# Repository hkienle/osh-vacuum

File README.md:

# Open Source Vacuum Cleaner

> **📝 Note:** This repository is currently being populated with information. Content and documentation are being added progressively.

---

## About

This repository contains the Open Source Vacuum Cleaner project, an open-source hardware and software solution for building custom vacuum cleaners. The project includes complete PCB designs, ESP32-S3 based firmware, and a web-based control interface.

The system is designed to control high RPM impellers for vacuum machines, featuring motor control, real-time monitoring (RPM, temperature, battery voltage), WiFi connectivity, and a modern web interface.

## Project Structure

```
osh-vacuum/
├── Hardware/              # PCB designs and hardware documentation
│   └── PCB_Bench_Prototype/  # Benchtop prototype board design
│       ├── README.md         # Hardware documentation and BOM
│       └── Production/       # Manufacturing files
├── Firmware/              # ESP32-S3 firmware and web interface
│   ├── README.md          # Firmware documentation, pin assignments, build instructions
│   ├── src/               # Firmware source code
│   └── ui/                # React-based web interface
└── README.md              # This file
```

### Hardware

The hardware design includes:
- ESP32-S3 microcontroller with WiFi and BLE
- Motor control with Infineon ProFet for high-side switching
- 5 RGB LEDs (WS2812B) and 3 customizable buttons
- Battery voltage monitoring (15-32V input)
- Temperature monitoring via thermistor
- Tachometer input for RPM measurement
- Break-off sections for flexible form factors

📖 **[Hardware Documentation →](Hardware/PCB_Bench_Prototype/README.md)**

### Firmware

The firmware provides:
- Motor speed control (0-100% PWM)
- Real-time monitoring (RPM, temperature, battery voltage)
- WiFi access point with web server
- WebSocket communication for live updates
- React-based web interface

📖 **[Firmware Documentation →](Firmware/README.md)**

## Quick Start

1. **Hardware**: Review the [PCB documentation](Hardware/PCB_Bench_Prototype/README.md) for board assembly
2. **Firmware**: Follow the [firmware build and upload instructions](Firmware/README.md)
3. **Frontend**: Build and upload the web interface as described in the firmware README

## Status

**Current Phase**: Benchtop Prototype

The current board design is untested and represents the benchtop prototype phase. All designs and firmware are provided as-is for development and testing purposes.

## License

This project is licensed under the **CERN Open Hardware Licence - Strongly Reciprocal (CERN OHL-S v2)**.

The full license text is available at: [cern_ohl_s_v2.txt](https://gitlab.com/ohwr/project/cernohl/-/wikis/uploads/819d71bea3458f71fba6cf4fb0f2de6b/cern_ohl_s_v2.txt)

---

*More information at [HackMD - Team Intuity](https://hackmd.io/@team-intuity) and [HackMD - hkienle](https://hackmd.io/@hkienle)*

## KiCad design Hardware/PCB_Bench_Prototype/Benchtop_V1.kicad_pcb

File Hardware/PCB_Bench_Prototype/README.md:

# PCB Bench Prototype

**Status: Untested** - This board is currently in the benchtop prototype phase of the Open Source Vacuum Cleaner project and has not yet been tested.

## Overview

This PCB is designed to control a high RPM impeller for vacuum machines. It provides comprehensive control and monitoring capabilities with modern connectivity options.

The design features break-off sections that allow users to build their own vacuum cleaner in whichever shape they like. These break-off sections enable flexible placement of LEDs and buttons to suit various form factors and user preferences.

## Features

- **Connectivity**
  - BLE (Bluetooth Low Energy)
  - WiFi connectivity
  
- **Power Management**
  - USB-C connector for programming
  - Voltage regulation from 15-32V down to 5V and 3.3V
  - Battery voltage monitoring (reads voltage of connected battery)
  
- **User Interface**
  - 5 RGB LEDs (WS2812B)
  - 3 customizable buttons
  
- **Motor Control & Monitoring**
  - Automotive ProFet by Infineon for high-side switching (required for ESC control, replacing classic MOSFETs)
  - Level-shifted 3.3V and 5V PWM output
  - Voltage-divided input for 5V tachometer signal
  - 10kΩ thermistor reading capability
  
- **Expansion**
  - All unused and safe GPIOs are broken out
  - I2C, SPI, and UART interfaces available

## Bill of Materials (BOM)

| Designator | Footprint | Quantity | Value | LCSC Part # |
|------------|-----------|----------|-------|-------------|
| C1, C7, C8, C9 | 0805 | 4 | 22µF | - |
| C10, C11, C12, C13, C14, C2, C5 | 0805 | 7 | 0.1µF | - |
| C3 | 0805 | 1 | 1µF | - |
| C4 | 0805 | 1 | 10nF | - |
| C6 | 0805 | 1 | 10µF | - |
| LED1, LED2, LED3, LED4, LED5 | LED-SMD_4P-L5.0-W5.0-TL-1 | 5 | WS2812B-V5/W | C2874885 |
| R10 | 0805 | 1 | 330kΩ | - |
| R11 | 0805 | 1 | 33kΩ | - |
| R12 | 0805 | 1 | 56kΩ | - |
| R13 | 0805 | 1 | 4.7kΩ | - |
| R14, R16 | 0805 | 2 | 5.1kΩ | - |
| R15, R17, R18, R3, R5, R6, R7, R8 | 0805 | 8 | 10kΩ | - |
| R4 | 0805 | 1 | 220Ω | - |
| R9 | 0805 | 1 | 22kΩ | - |
| SW1, SW2 | SW-SMD_4P-L4.2-W3.2-P2.15-LS4.6 | 2 | RKB2SJK250SMTRLFS | C2927789 |
| SW6, SW7, SW8 | KEY-SMD_4P-L5.2-W5.2-P3.7-LS6.4-TL | 3 | TS-1076S-A7B3 | C492950 |
| U1 | WIRELM-SMD_ESP32-S3-WROOM-1 | 1 | ESP32-S3-WROOM-1(N16R2) | C2913205 |
| U2 | PG-HSOF-8_L10.4-W9.8-BTH500151LUAAUMA1 | 1 | BTH500151LUAAUMA1 | C36571656 |
| U3 | SOT-223-4_L6.5-W3.5-P2.30-LS7.0-BR | 1 | LD1117S33CTR | C35879 |
| U4, U5 | SC-70-5_L2.0-W1.3-P0.65-LS2.1-BL | 2 | SN74AHCT1G125DCKR | C350557 |
| U8 | PWRM-TH_L11.7-W7.5_TSR1-2450 | 1 | TSR 1-2450_C6886877 | C6886877 |
| U9 | USB-SMD_TYPE-C16PIN-1 | 1 | 12402012E212A | C5150972 |

## Images

### Front View

### Back View

### PCB Layout

## License

This hardware design is licensed under the **CERN Open Hardware Licence - Strongly Reciprocal (CERN OHL-S v2)**.

The full license text is available at: [cern_ohl_s_v2.txt](https://gitlab.com/ohwr/project/cernohl/-/wikis/uploads/819d71bea3458f71fba6cf4fb0f2de6b/cern_ohl_s_v2.txt)

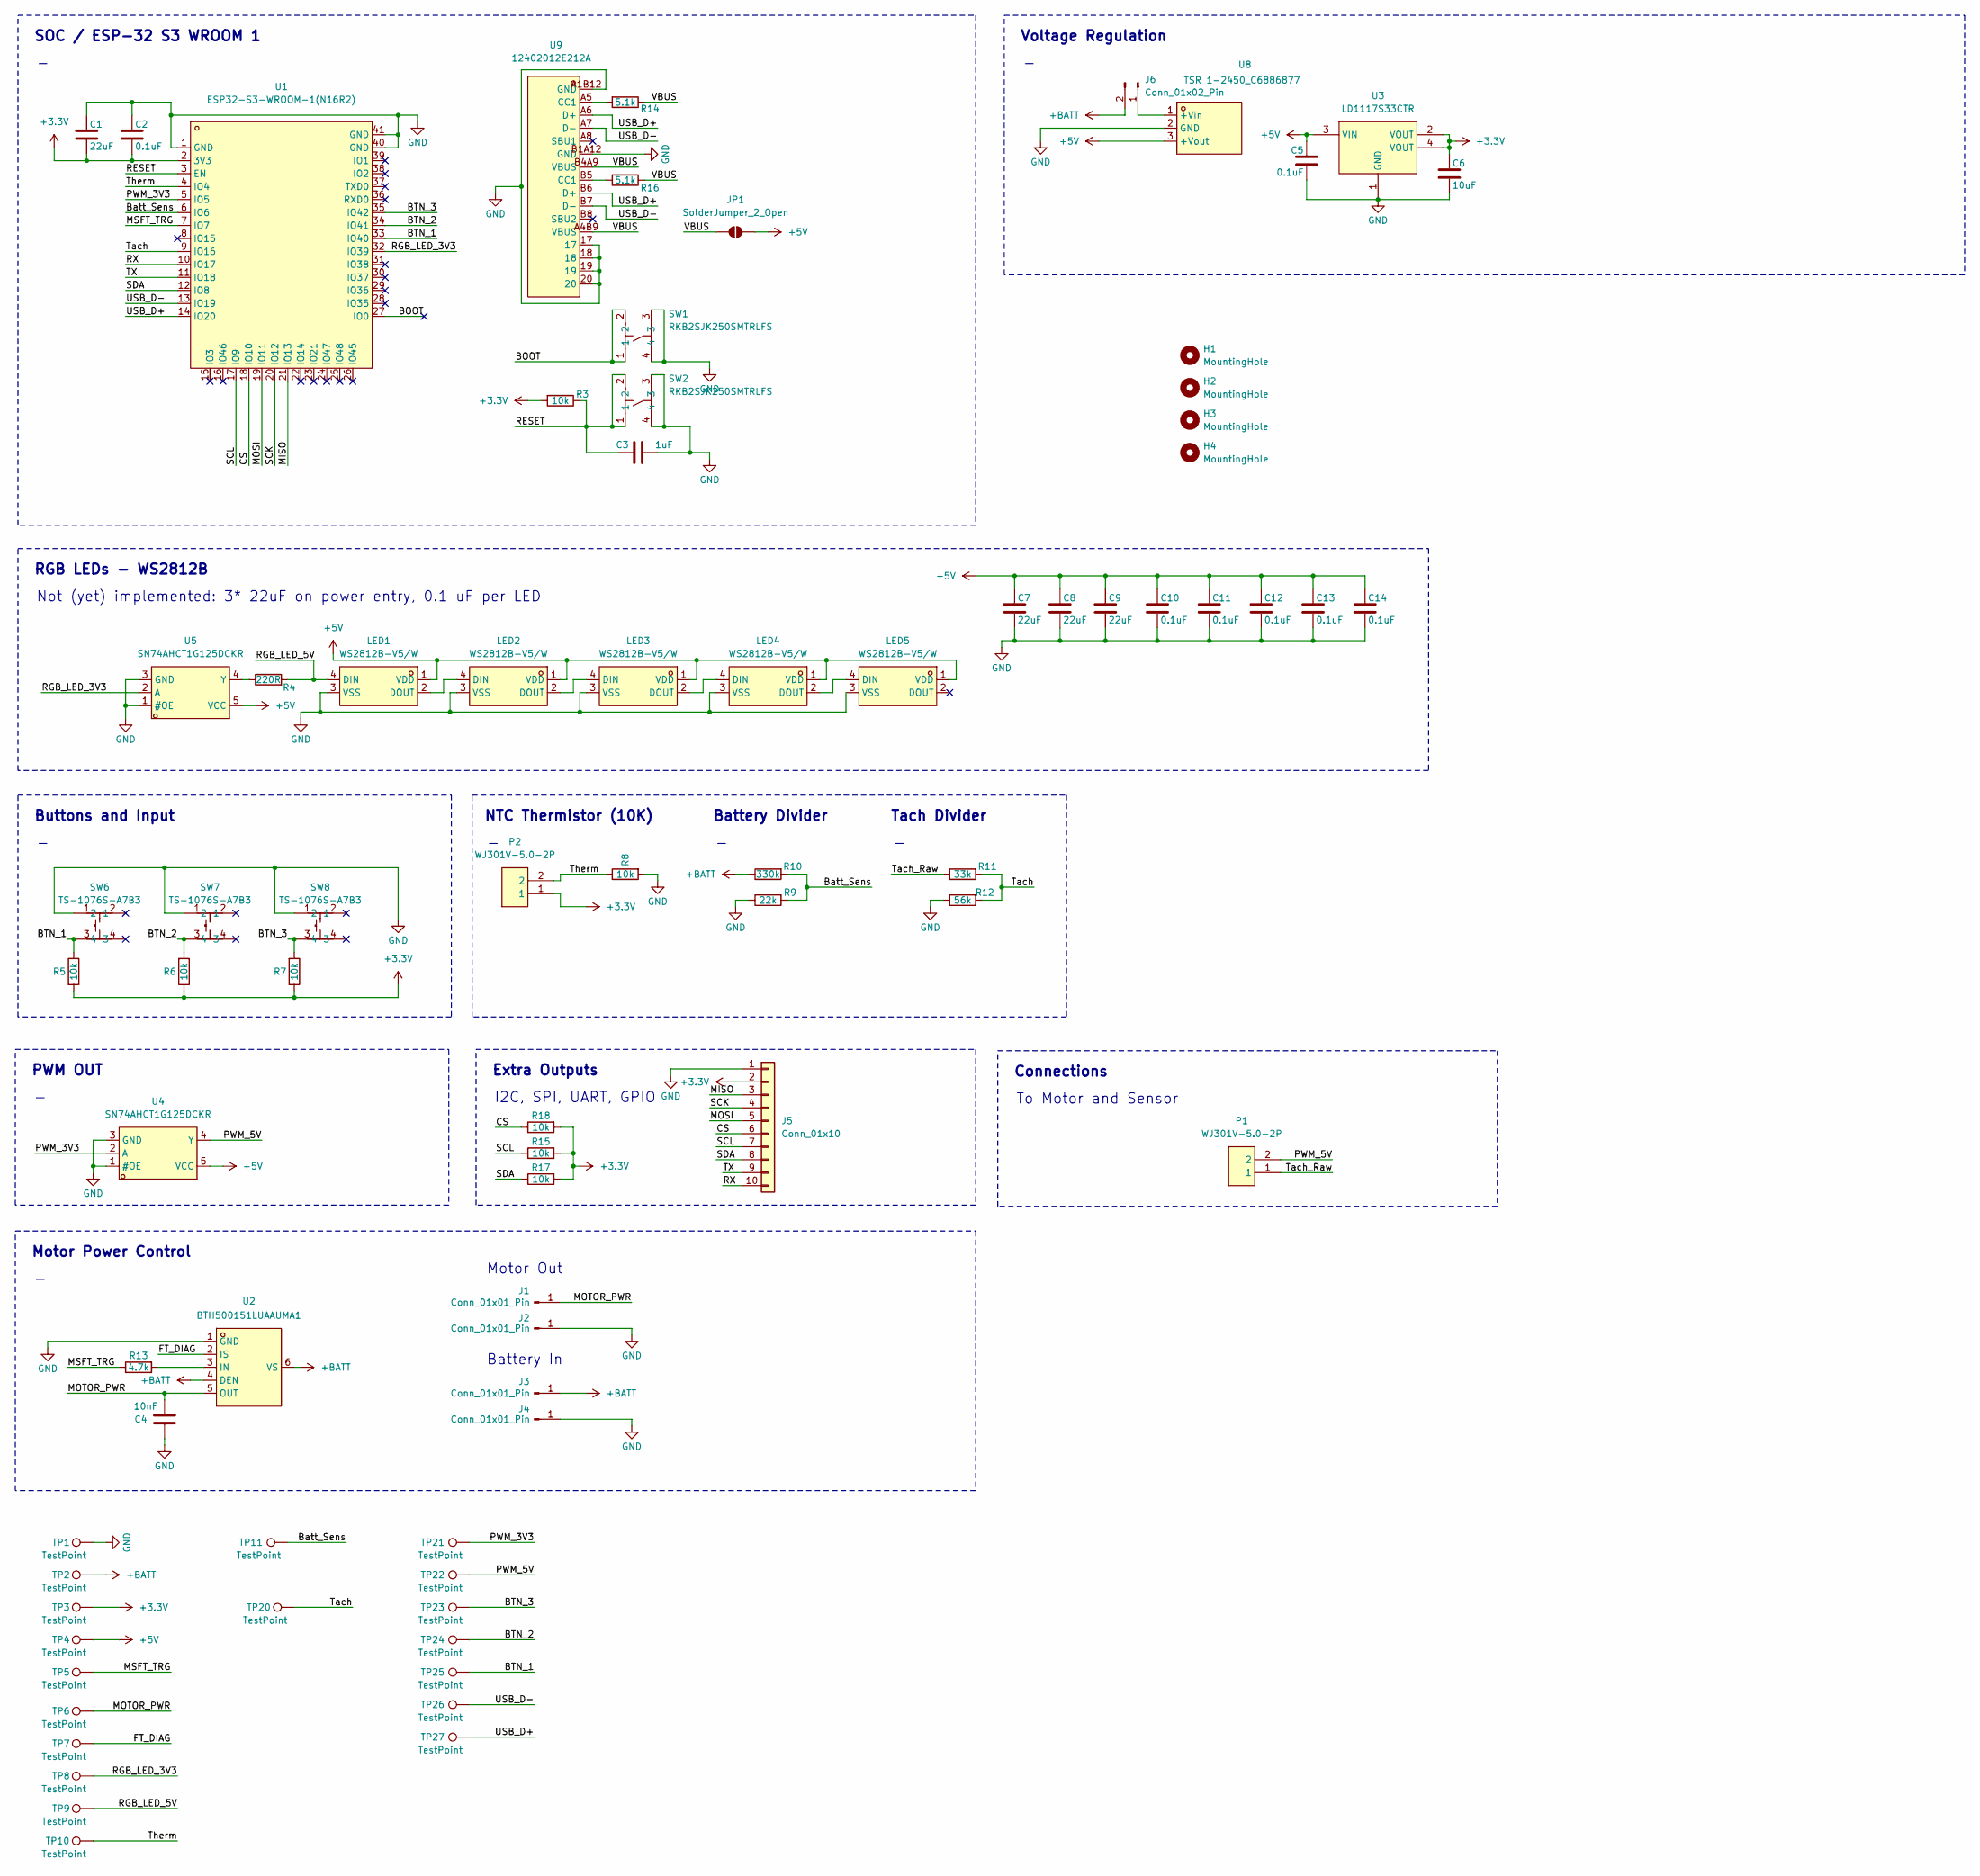
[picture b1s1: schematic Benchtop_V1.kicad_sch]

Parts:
C1, C7, C8, C9: 22uF; R_0805_2012Metric_Pad1.20x1.40mm_HandSolder
C2, C5, C10, C11, C12, C13, C14: 0.1uF; R_0805_2012Metric_Pad1.20x1.40mm_HandSolder
C3: 1uF; R_0805_2012Metric_Pad1.20x1.40mm_HandSolder
C4: 10nF; R_0805_2012Metric_Pad1.20x1.40mm_HandSolder
C6: 10uF; R_0805_2012Metric_Pad1.20x1.40mm_HandSolder
H1, H2, H3, H4: MountingHole; MountingHole_3.2mm_M3_Pad_Via
J1, J2, J3, J4: Conn_01x01_Pin; SolderWirePad_1x01_SMD_5x10mm
J5: Conn_01x10; PinHeader_2x05_P2.54mm_Vertical
J6: Conn_01x02_Pin; PinHeader_1x02_P2.54mm_Vertical
JP1: SolderJumper_2_Open; SolderJumper-2_P1.3mm_Open_Pad1.0x1.5mm
LED1, LED2, LED3, LED4, LED5: WS2812B-V5/W; LED-SMD_4P-L5.0-W5.0-TL-1; LCSC Part C2874885
P1, P2: WJ301V-5.0-2P; CONN-TH_2P-P5.00_WJ301V-5.00-2P; LCSC Part C8475
R3, R5, R6, R7, R8, R15, R17, R18: 10k; R_0805_2012Metric_Pad1.20x1.40mm_HandSolder
R4: 220R; R_0805_2012Metric_Pad1.20x1.40mm_HandSolder
R9: 22k; R_0805_2012Metric_Pad1.20x1.40mm_HandSolder
R10: 330k; R_0805_2012Metric_Pad1.20x1.40mm_HandSolder
R11: 33k; R_0805_2012Metric_Pad1.20x1.40mm_HandSolder
R12: 56k; R_0805_2012Metric_Pad1.20x1.40mm_HandSolder
R13: 4.7k; R_0805_2012Metric_Pad1.20x1.40mm_HandSolder
R14, R16: 5.1k; R_0805_2012Metric_Pad1.20x1.40mm_HandSolder
SW1, SW2: RKB2SJK250SMTRLFS; SW-SMD_4P-L4.2-W3.2-P2.15-LS4.6; LCSC Part C2927789
SW6, SW7, SW8: TS-1076S-A7B3; KEY-SMD_4P-L5.2-W5.2-P3.7-LS6.4-TL; LCSC Part C492950
TP1, TP2, TP3, TP4, TP5, TP6, TP7, TP8, TP9, TP10, TP11, TP20, TP21, TP22, TP23, TP24, TP25, TP26, TP27: TestPoint; TestPoint_Pad_D1.0mm
U1: ESP32-S3-WROOM-1(N16R2); WIRELM-SMD_ESP32-S3-WROOM-1; LCSC Part C2913205
U2: BTH500151LUAAUMA1; PG-HSOF-8_L10.4-W9.8-BTH500151LUAAUMA1; LCSC Part C36571656
U3: LD1117S33CTR; SOT-223-4_L6.5-W3.5-P2.30-LS7.0-BR; LCSC Part C35879
U4, U5: SN74AHCT1G125DCKR; SC-70-5_L2.0-W1.3-P0.65-LS2.1-BL; LCSC Part C350557
U8: TSR 1-2450_C6886877; PWRM-TH_L11.7-W7.5_TSR1-2450; LCSC Part C6886877
U9: 12402012E212A; USB-SMD_TYPE-C16PIN-1; LCSC Part C5150972

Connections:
+3.3V: C1.2, C2.2, C6.1, J5.2, P2.1, R3.2, R5.2, R6.1, R7.1, R15.2, R17.2, R18.2, TP3.1, U1.2 (3V3), U3.2 (VOUT), U3.4 (VOUT)
+5V: C5.1, C7.1, C8.1, C9.1, C10.1, C11.1, C12.1, C13.1, C14.1, JP1.2 (B), LED1.1 (VDD), LED2.1 (VDD), LED3.1 (VDD), LED4.1 (VDD), LED5.1 (VDD), TP4.1, U3.3 (VIN), U4.5 (VCC), U5.5 (VCC), U8.3 (+Vout)
+BATT: J3.1, J6.2, R10.1, TP2.1, U2.4 (DEN), U2.6 (VS)
/BOOT: SW1.1, SW1.2, U1.27 (IO0)
/BTN_1: R5.1, SW6.3, TP25.1, U1.33 (IO40)
/BTN_2: R6.2, SW7.3, TP24.1, U1.34 (IO41)
/BTN_3: R7.2, SW8.3, TP23.1, U1.35 (IO42)
/Batt_Sens: R9.2, R10.2, TP11.1, U1.6 (IO6)
/CS: J5.6, R18.1, U1.18 (IO10)
/FT_DIAG: TP7.1, U2.2 (IS)
/MISO: J5.3, U1.21 (IO13)
/MOSI: J5.5, U1.19 (IO11)
/MOTOR_PWR: C4.2, J1.1, TP6.1, U2.5 (OUT)
/MSFT_TRG: R13.1, TP5.1, U1.7 (IO7)
/PWM_3V3: TP21.1, U1.5 (IO5), U4.2 (A)
/PWM_5V: P1.2, TP22.1, U4.4 (Y)
/RESET: C3.1, R3.1, SW2.1, SW2.2, U1.3 (EN)
/RGB_LED_3V3: TP8.1, U1.32 (IO39), U5.2 (A)
/RGB_LED_5V: LED1.4 (DIN), R4.2, TP9.1
/RX: J5.10, U1.10 (IO17)
/SCK: J5.4, U1.20 (IO12)
/SCL: J5.7, R15.1, U1.17 (IO9)
/SDA: J5.8, R17.1, U1.12 (IO8)
/TX: J5.9, U1.11 (IO18)
/Tach: R11.2, R12.2, TP20.1, U1.9 (IO16)
/Tach_Raw: P1.1, R11.1
/Therm: P2.2, R8.1, TP10.1, U1.4 (IO4)
/USB_D+: TP27.1, U1.14 (IO20), U9.A6 (D+), U9.B6 (D+)
/USB_D-: TP26.1, U1.13 (IO19), U9.A7 (D-), U9.B7 (D-)
/VBUS: JP1.1 (A), R14.1, R16.1, U9.A4B9 (VBUS), U9.B4A9 (VBUS)
GND: C1.1, C2.1, C3.2, C4.1, C5.2, C6.2, C7.2, C8.2, C9.2, C10.2, C11.2, C12.2, C13.2, C14.2, J2.1, J4.1, J5.1, LED1.3 (VSS), LED2.3 (VSS), LED3.3 (VSS), LED4.3 (VSS), LED5.3 (VSS), R8.2, R9.1, R12.1, SW1.3, SW1.4, SW2.3, SW2.4, SW6.1, SW7.1, SW8.1, TP1.1, U1.1 (GND), U1.40 (GND), U1.41 (GND), U2.1 (GND), U3.1 (GND), U4.1 (#OE), U4.3 (GND), U5.1 (#OE), U5.3 (GND), U8.2 (GND), U9.17, U9.18, U9.19, U9.20, U9.A1B12 (GND), U9.B1A12 (GND)
unnamed: J6.1, U8.1 (+Vin)
unnamed: LED1.2 (DOUT), LED2.4 (DIN)
unnamed: LED2.2 (DOUT), LED3.4 (DIN)
unnamed: LED3.2 (DOUT), LED4.4 (DIN)
unnamed: LED4.2 (DOUT), LED5.4 (DIN)
unnamed: R14.2, U9.A5 (CC1)
unnamed: R16.2, U9.B5 (CC1)
unnamed: R13.2, U2.3 (IN)
unnamed: R4.1, U5.4 (Y)

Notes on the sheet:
PWM OUT
NTC Thermistor (10K)
Buttons and Input
Extra Outputs
Voltage Regulation
Motor Out
RGB LEDs - WS2812B
To Motor and Sensor
SOC / ESP-32 S3 WROOM 1
Motor Power Control
Not (yet) implemented: 3* 22uF on power entry, 0.1 uF per LED
Battery Divider
Battery In
I2C, SPI, UART, GPIO
Connections
Tach Divider

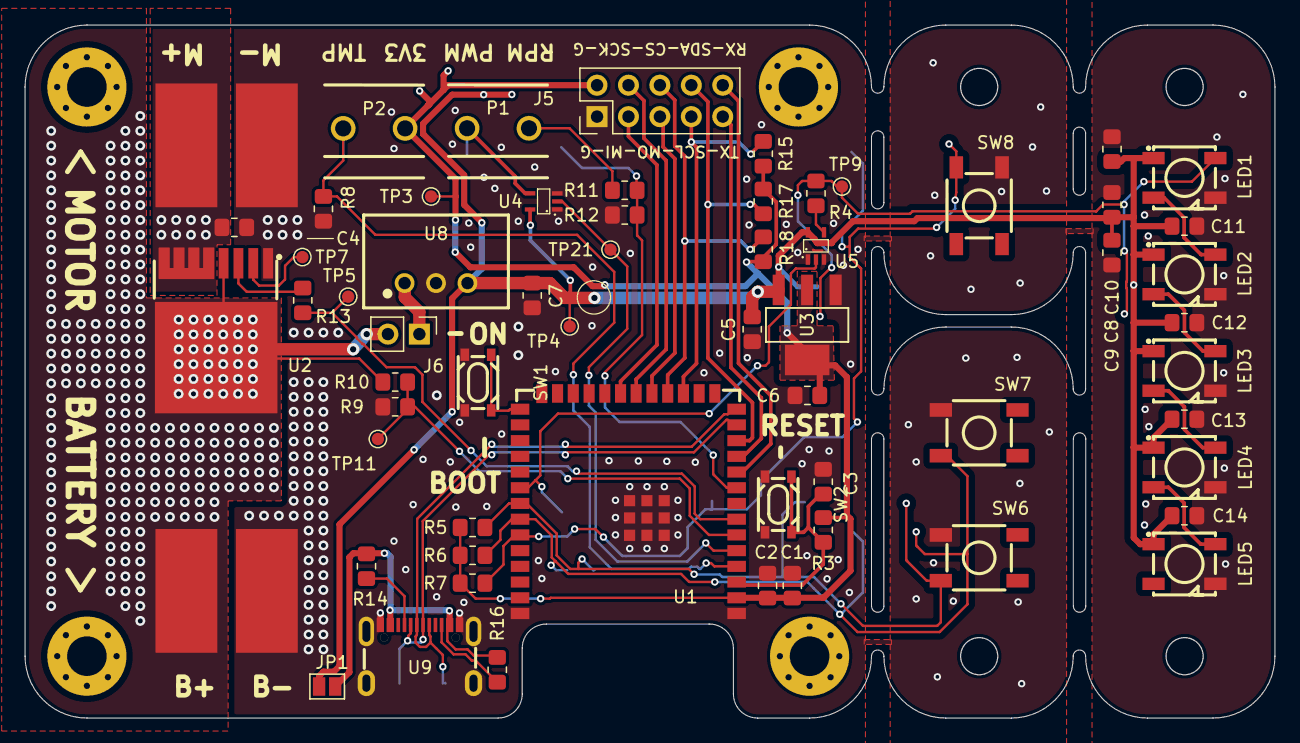
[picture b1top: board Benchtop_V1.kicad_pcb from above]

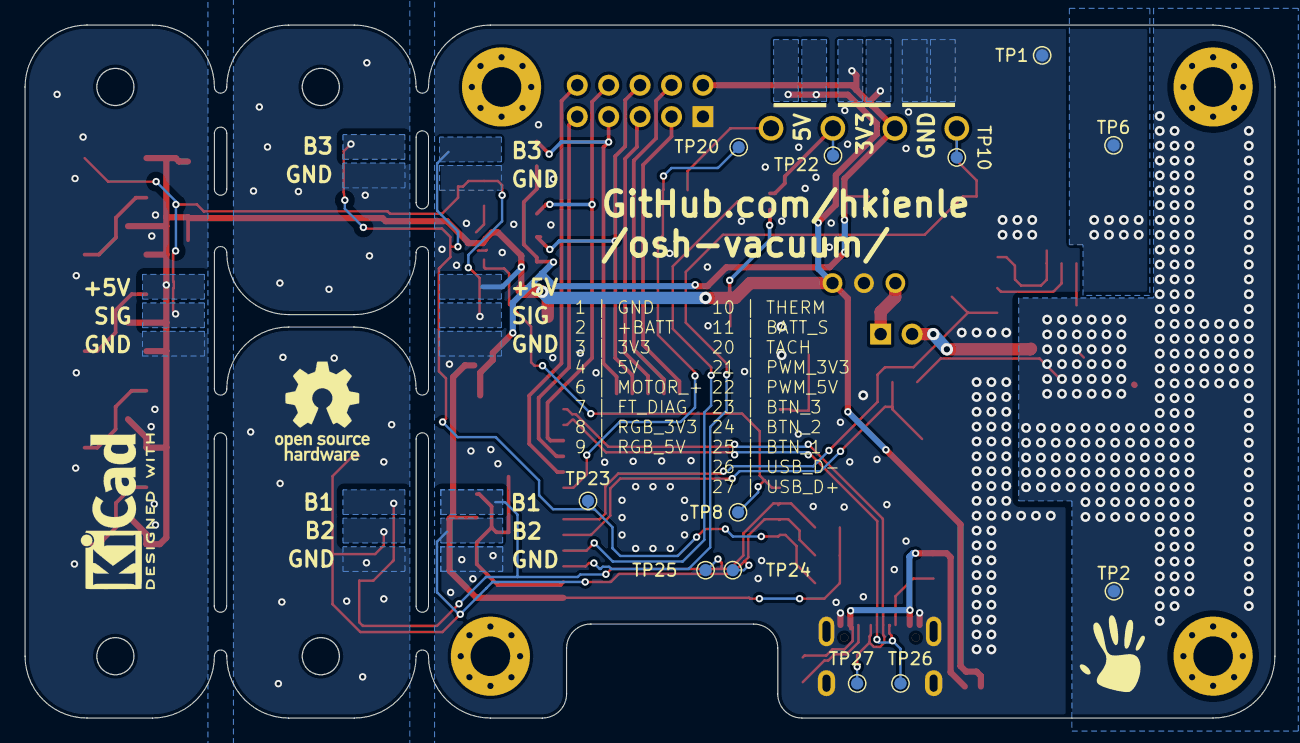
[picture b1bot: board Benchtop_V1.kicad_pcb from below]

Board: 2 copper layers, 101.0 x 56.0 mm, 79 parts (12 on the bottom side), 40 nets.

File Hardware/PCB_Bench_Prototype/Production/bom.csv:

Designator,Footprint,Quantity,Value,LCSC Part #
"C1, C7, C8, C9",0805,4,22uF,
"C10, C11, C12, C13, C14, C2, C5",0805,7,0.1uF,
C3,0805,1,1uF,
C4,0805,1,10nF,
C6,0805,1,10uF,
"J1, J2, J3, J4",SolderWirePad_1x01_SMD_5x10mm,4,Conn_01x01_Pin,
J5,PinHeader_2x05_P2.54mm_Vertical,1,Conn_01x10,
J6,PinHeader_1x02_P2.54mm_Vertical,1,Conn_01x02_Pin,
"LED1, LED2, LED3, LED4, LED5",LED-SMD_4P-L5.0-W5.0-TL-1,5,WS2812B-V5/W,C2874885
"P1, P2",CONN-TH_2P-P5.00_WJ301V-5.00-2P,2,WJ301V-5.0-2P,C8475
R10,0805,1,330k,
R11,0805,1,33k,
R12,0805,1,56k,
R13,0805,1,4.7k,
"R14, R16",0805,2,5.1k,
"R15, R17, R18, R3, R5, R6, R7, R8",0805,8,10k,
R4,0805,1,220R,
R9,0805,1,22k,
"SW1, SW2",SW-SMD_4P-L4.2-W3.2-P2.15-LS4.6,2,RKB2SJK250SMTRLFS,C2927789
"SW6, SW7, SW8",KEY-SMD_4P-L5.2-W5.2-P3.7-LS6.4-TL,3,TS-1076S-A7B3,C492950
"TP1, TP10, TP11, TP2, TP20, TP21, TP22, TP23, TP24, TP25, TP26, TP27, TP3, TP4, TP5, TP6, TP7, TP8, TP9",TestPoint_Pad_D1.0mm,19,TestPoint,
U1,WIRELM-SMD_ESP32-S3-WROOM-1,1,ESP32-S3-WROOM-1(N16R2),C2913205
U2,PG-HSOF-8_L10.4-W9.8-BTH500151LUAAUMA1,1,BTH500151LUAAUMA1,C36571656
U3,SOT-223-4_L6.5-W3.5-P2.30-LS7.0-BR,1,LD1117S33CTR,C35879
"U4, U5",SC-70-5_L2.0-W1.3-P0.65-LS2.1-BL,2,SN74AHCT1G125DCKR,C350557
U8,PWRM-TH_L11.7-W7.5_TSR1-2450,1,TSR 1-2450_C6886877,C6886877
U9,USB-SMD_TYPE-C16PIN-1,1,12402012E212A,C5150972

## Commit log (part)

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2025-11-27 Added KiCad and manufacturing files for the benchtop PCB V1.0
2025-12-15 Added firmware
2025-12-15 Updated readme files
2026-04-15 Display integration, highly functional update.
2026-04-15 Updat readme
2026-04-20 add printed parts
2026-04-20 moved printfiles into correct dir
2026-04-21 added mesh part for the cyclone
2026-04-21 Updated Core skrew layout
2026-04-21 Added Holes for different skrew length in lid
2026-04-27 added flat nozzle variants
2026-04-27 renamed files to match BOM
2026-04-27 added Checklist for build overview
2026-04-27 added landing page
2026-04-27 Refactor index.html for VAC V1.x, replacing old styles and scripts with new ones, and updating the structure for the print checklist. Removed outdated checklist assets and added new functionality for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
2026-04-27 Update BOM metadata handling and add new part number validation features. Removed obsolete bom-meta.js file and integrated new part number schema checks and placeholder inference in bom-meta.ts. Upda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
2026-04-27 Add filtering options for mass and time in the workshop interface, update BOM metadata for purchased parts, and enhance rendering logic for purchased items.
2026-04-27 Enhance workshop interface with mass and time filtering inputs, update asset paths for deployment, and improve error handling in GitHub file fetching.
2026-04-27 Update asset paths in index.html and build/index.html, remove obsolete CSS and JS files, and enhance rendering logic with field suggestion datalists for improved user experience in the workshop inter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
2026-04-28 Enhance landing page with 3D background rendering, update styles for improved UI, and add new project documentation links. Introduce new GLTF model for visual representation and optimize button inter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
2026-04-28 Update Vite dependency metadata with new hash values for improved build integrity.
2026-04-28 Refactor asset management in index.html and build/index.html, update script and stylesheet paths, remove obsolete files, and enhance error handling in GitHub file fetching. Introduce new CSS and JS f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
2026-04-29 Remove PlatformIO auto-generated VSCode files from tracking
2026-04-29 Integrate maximum stats functionality into firmware. Updated display and button handling to support new settings for maximum duty, LED themes, and telemetry. Enhanced LED behavior for OTA updates and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
2026-04-29 First variant of a UART controller.
2026-04-30 added cart and wallmount, moved nozzle to new aux folder
2026-04-30 made the cable channel bigger
2026-04-30 Converting step to stl files
    Converting .step to .stl files via python script using FreeCADCmd command line tool. Requires freecadcmd to be installed and in the PATH of your shell.
2026-05-05 removed cable divider in the bottom to avoid pinching
2026-05-05 added .stl files for each .step file
    As my printer does not support .step and Mac finder allows preview of .stl I added them in the same folder structure.
2026-05-05 added hose adapter
2026-05-13 Add BOM for vacuum component assembly
    Added a Bill of Materials (BOM) for vacuum component assembly, including printed parts, metal hardware, and additional parts with procurement details.
2026-05-22 Change motor behaviour
2026-06-18 switch to 1.5 inch display
2026-06-19 add display sim to the project
2026-06-19 Refactor documentation for MAC build setup and display architecture. Improved formatting for clarity and consistency across tables, enhancing readability of build status, UI components, and related f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
2026-06-19 new hosted webUI for bluetooth connection
2026-06-23 Add Mac build setup notes and PlatformIO IDE recommendations
2026-06-24 Add data overview and roadmap for floor detection
2026-06-24 Add data overview and roadmap for floor detection (#13)
2026-06-26 Update floor detection roadmap
2026-06-26 Update floor detection roadmap (#14)
